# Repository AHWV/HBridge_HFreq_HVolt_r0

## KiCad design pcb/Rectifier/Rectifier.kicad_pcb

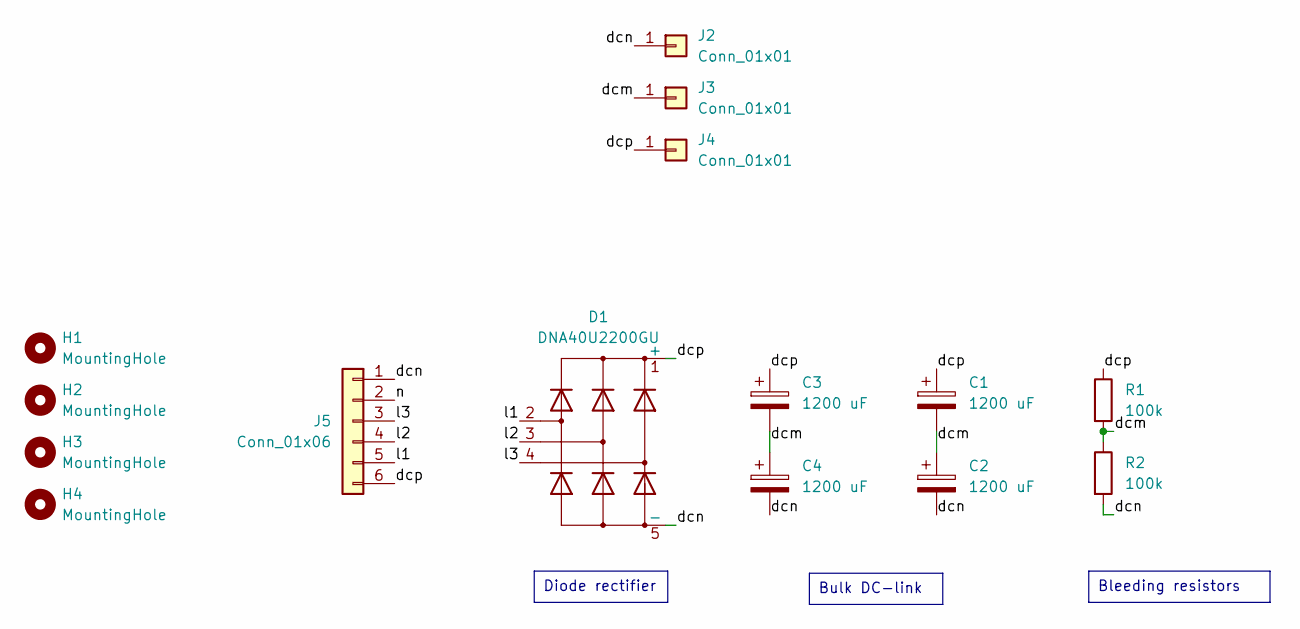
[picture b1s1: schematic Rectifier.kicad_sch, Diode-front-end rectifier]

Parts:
C1, C2, C3, C4: 1200 uF; CP_Radial_D35.0mm_P22.50mm_SnapIn_4Pin_TDK_B43630; Part # MAL229956122E3
D1: DNA40U2200GU; Diode_Bridge_IXYS_GUFP
H1, H2, H3, H4: MountingHole; MountingHole_2.7mm_M2.5
J2, J3, J4: Conn_01x01; WP_SMRA_7466303; Part # 7466303
J5: Conn_01x06; PhoenixContact_SPT_5_6-H-7.5-ZB_1x06_P7.5mm_Horizontal
R1, R2: 100k; R_Axial_DIN0617_L17.0mm_D6.0mm_P30.48mm_Horizontal

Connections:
/dcm: C1.2, C2.1, C3.2, C4.1, J3.1, R1.2, R2.1
/dcn: C2.2, C4.2, D1.5 (-), J2.1, J5.1, R2.2
/dcp: C1.1, C3.1, D1.1 (+), J4.1, J5.6, R1.1
/l1: D1.2, J5.5
/l2: D1.3, J5.4
/l3: D1.4, J5.3
/n: J5.2

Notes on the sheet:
Diode rectifier
Bulk DC-link
Bleeding resistors

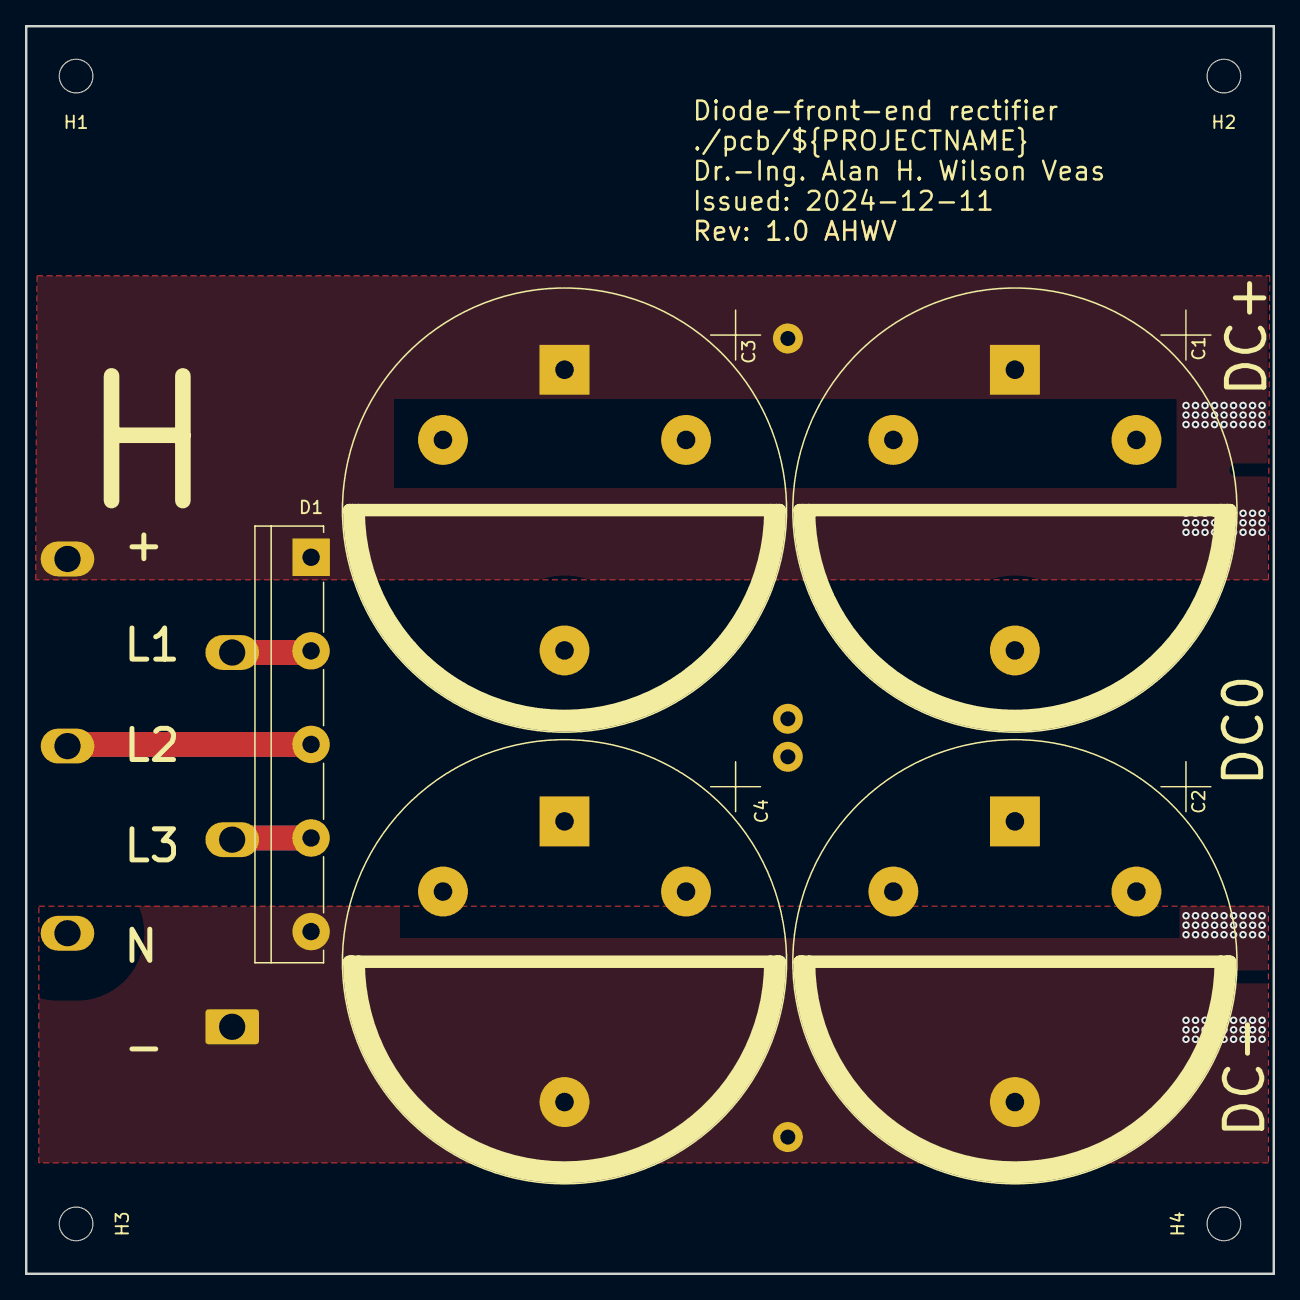
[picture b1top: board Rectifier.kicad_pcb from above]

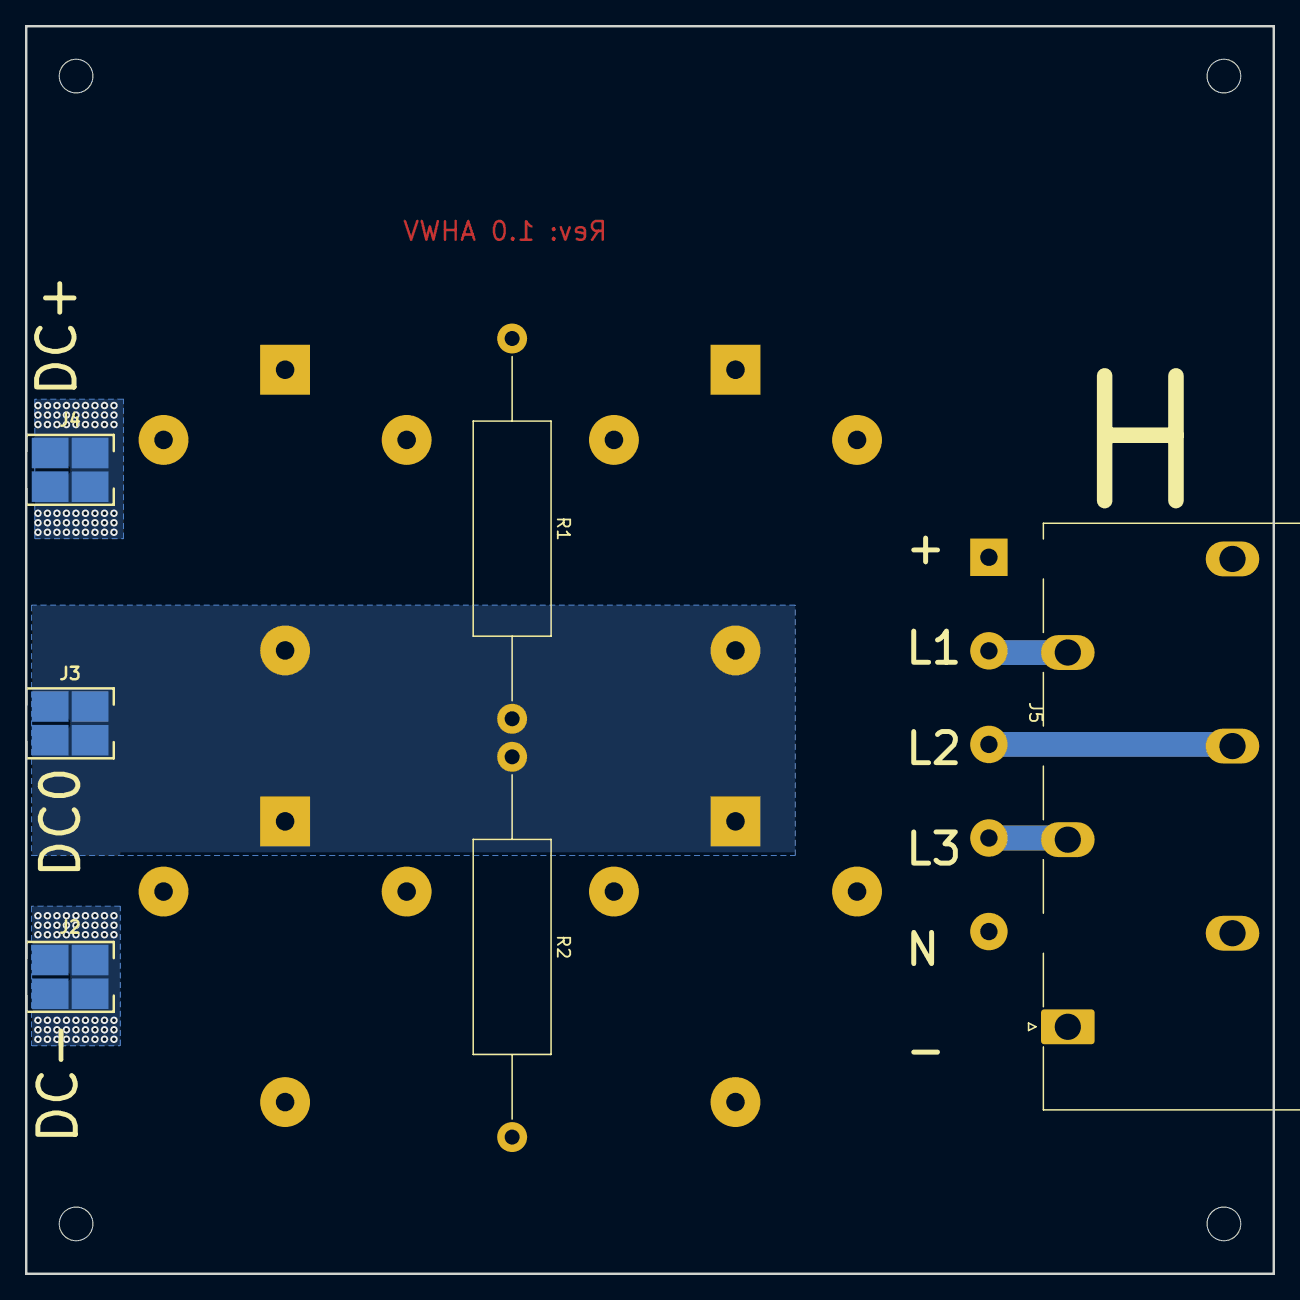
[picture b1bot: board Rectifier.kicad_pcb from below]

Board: 2 copper layers, 100.0 x 100.0 mm, 15 parts (6 on the bottom side), 6 nets.

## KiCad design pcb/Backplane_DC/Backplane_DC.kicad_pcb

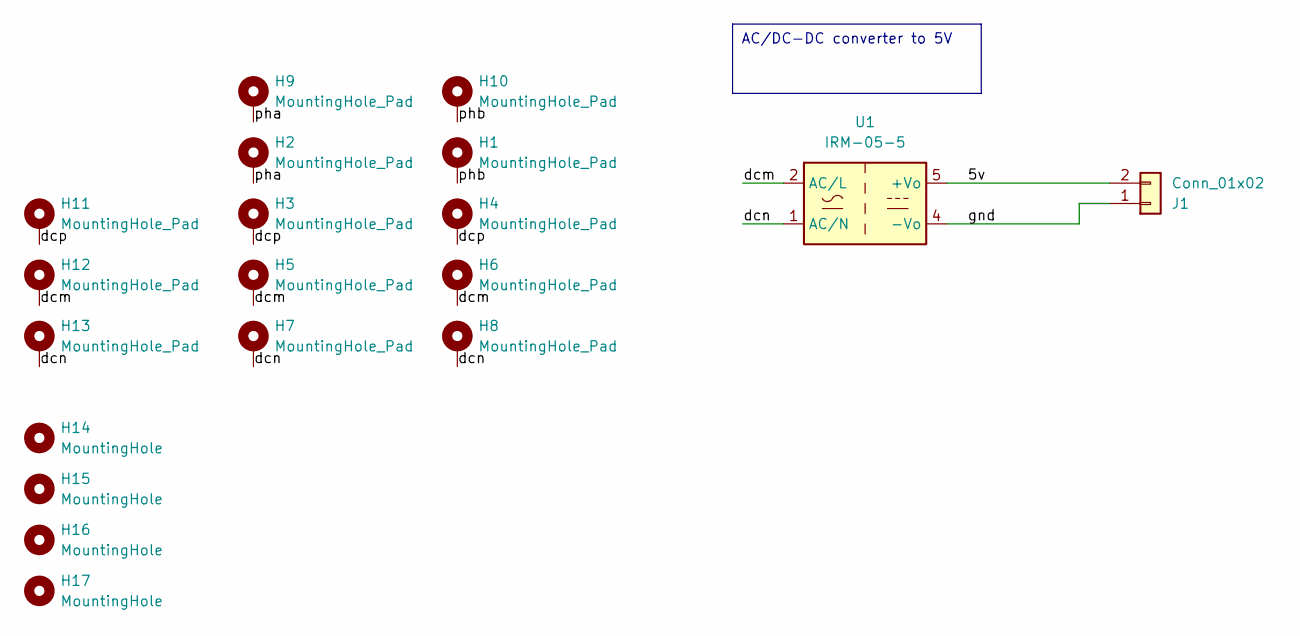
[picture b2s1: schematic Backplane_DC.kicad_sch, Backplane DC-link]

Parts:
H1, H2, H3, H4, H5, H6, H7, H8, H9, H10, H11, H12, H13: MountingHole_Pad; MountingHole_4.3mm_M4_DIN965_Pad
H14, H15, H16, H17: MountingHole; MountingHole_2.7mm_M2.5
J1: Conn_01x02; PhoenixContact_SPT_1.5_2-H-3.5_1x02_P3.5mm_Horizontal
U1: IRM-05-5

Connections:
/5v: J1.2, U1.5 (+Vo)
/dcm: H5.1, H6.1, H12.1, U1.2 (AC/L)
/dcn: H7.1, H8.1, H13.1, U1.1 (AC/N)
/dcp: H3.1, H4.1, H11.1
/gnd: J1.1, U1.4 (-Vo)
/pha: H2.1, H9.1
/phb: H1.1, H10.1

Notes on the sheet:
AC/DC-DC converter to 5V

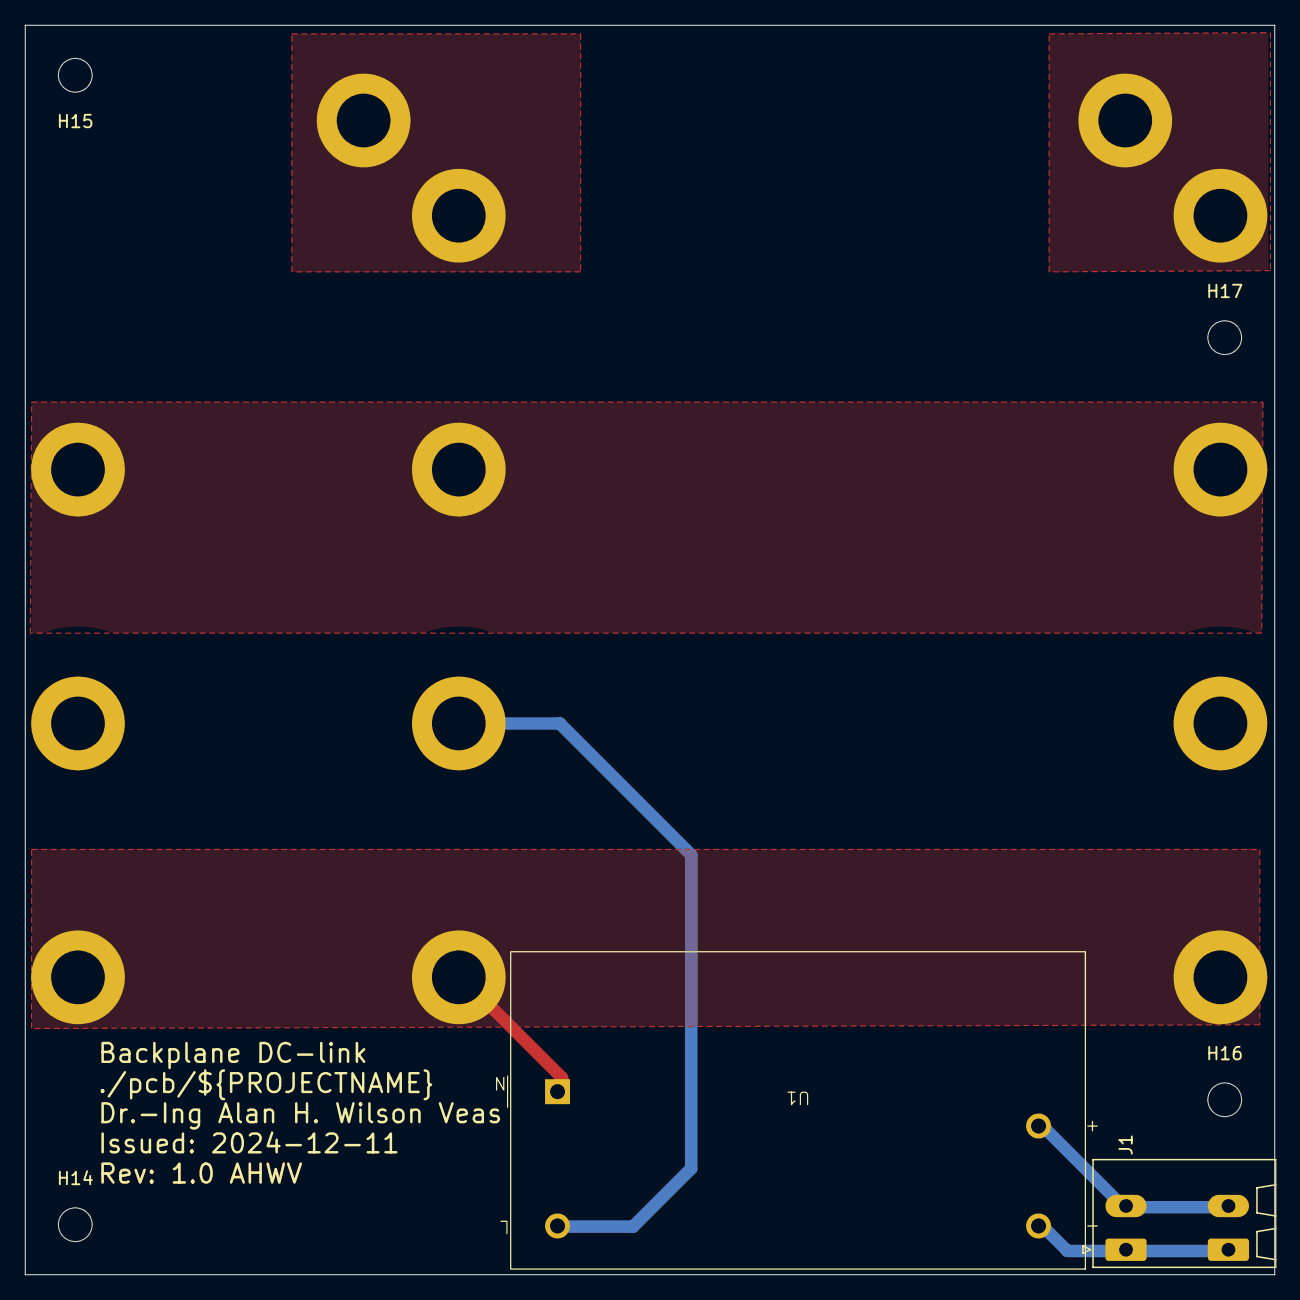
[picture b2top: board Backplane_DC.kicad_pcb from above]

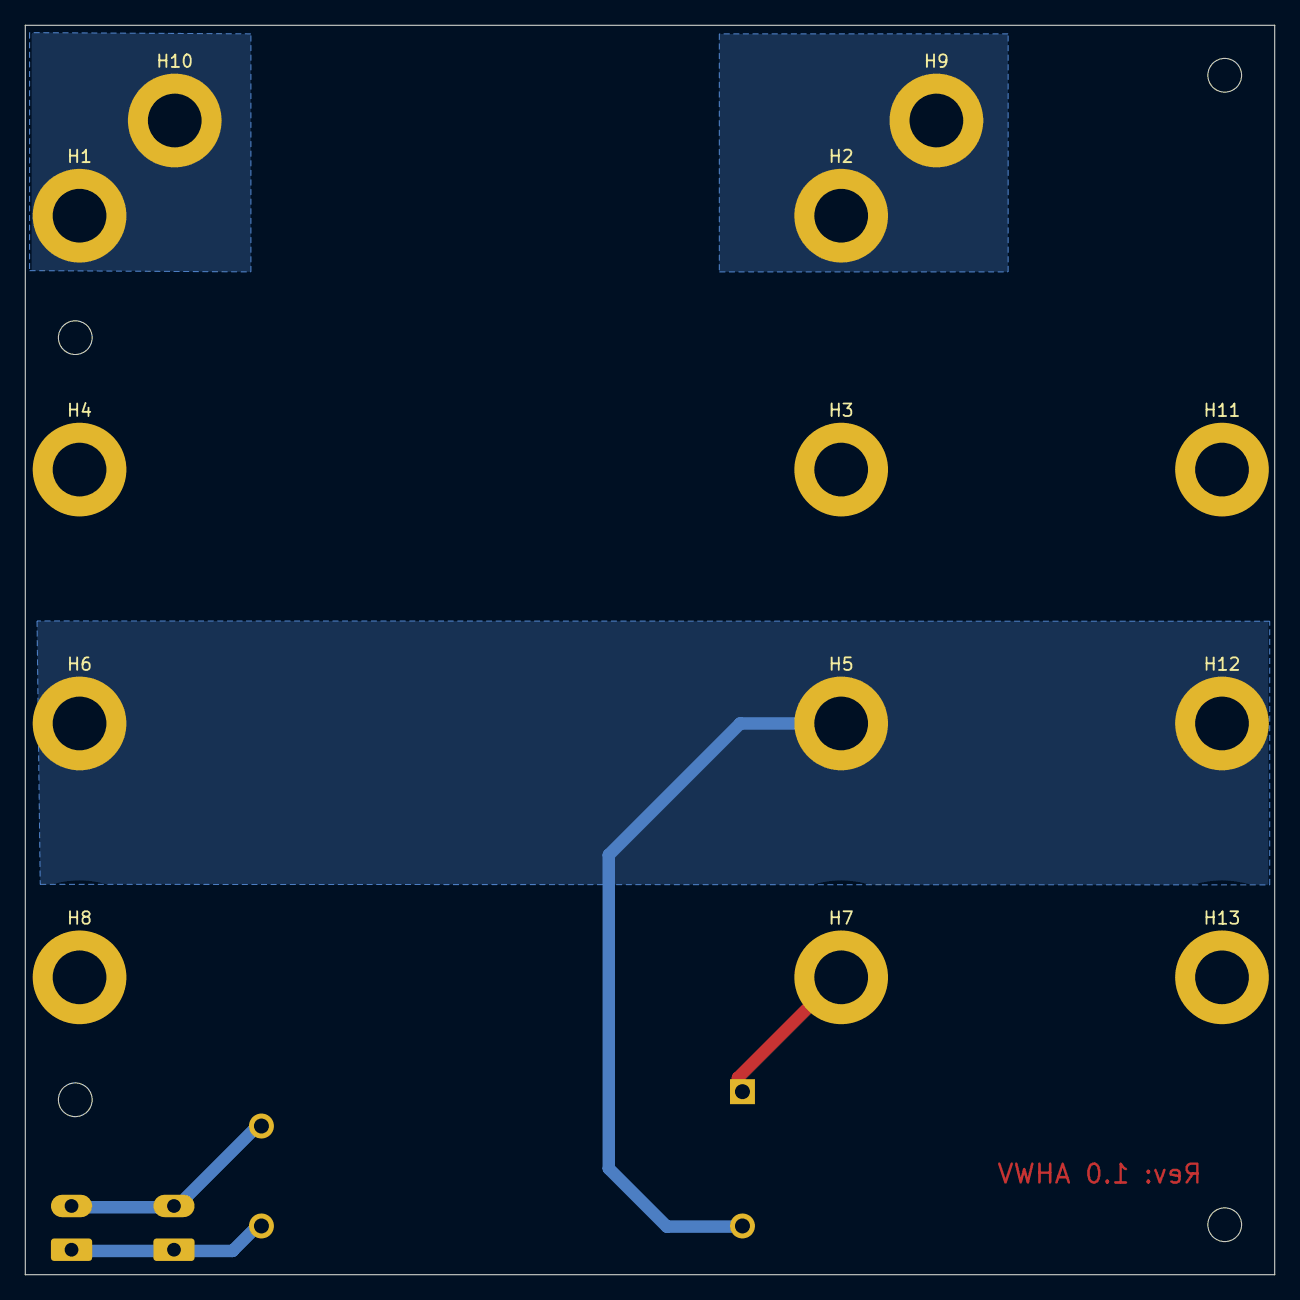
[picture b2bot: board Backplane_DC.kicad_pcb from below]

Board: 2 copper layers, 100.0 x 100.0 mm, 19 parts (13 on the bottom side), 7 nets.

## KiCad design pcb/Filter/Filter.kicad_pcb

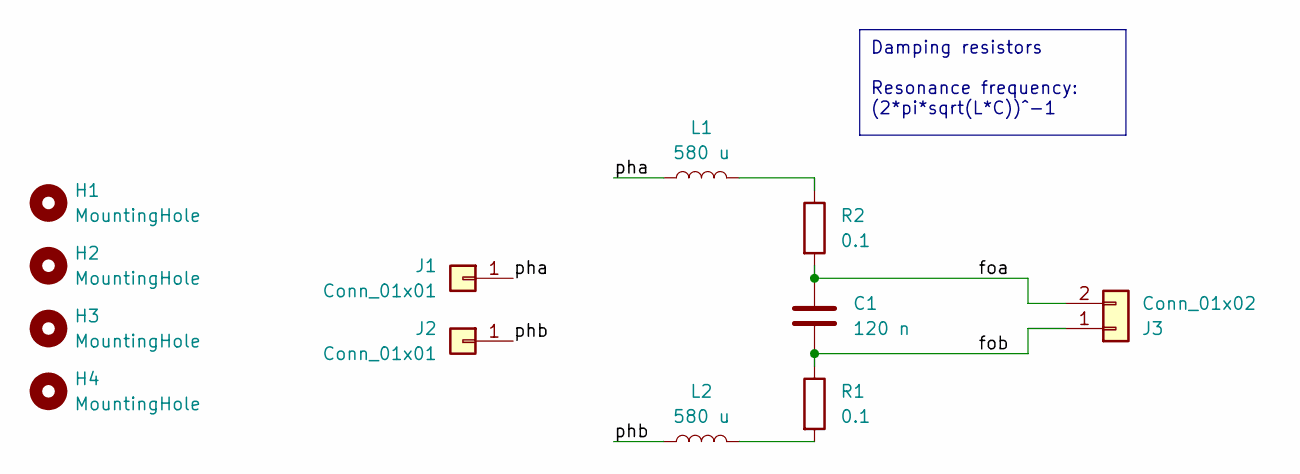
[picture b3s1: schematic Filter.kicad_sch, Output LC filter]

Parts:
C1: 120 n; C_Rect_L26.5mm_W11.5mm_P22.50mm_MKS4
H1, H2, H3, H4: MountingHole; MountingHole_2.7mm_M2.5
J1, J2: Conn_01x01; WP_SMRA_7466303; Part # 7466303
J3: Conn_01x02; PhoenixContact_SPT_5_2-H-7.5-ZB_1x02_P7.5mm_Horizontal
L1, L2: 580 u; L_Wuerth_WE-TORPFC_Diameter72.0mm_760801203
R1, R2: 0.1; R_Axial_DIN0617_L17.0mm_D6.0mm_P25.40mm_Horizontal

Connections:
/foa: C1.1, J3.2, R2.2
/fob: C1.2, J3.1, R1.1
/pha: J1.1, L1.1
/phb: J2.1, L2.1
unnamed: L1.2, R2.1
unnamed: L2.2, R1.2

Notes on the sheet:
Damping resistors Resonance frequency: (2*pi*sqrt(L*C))^-1

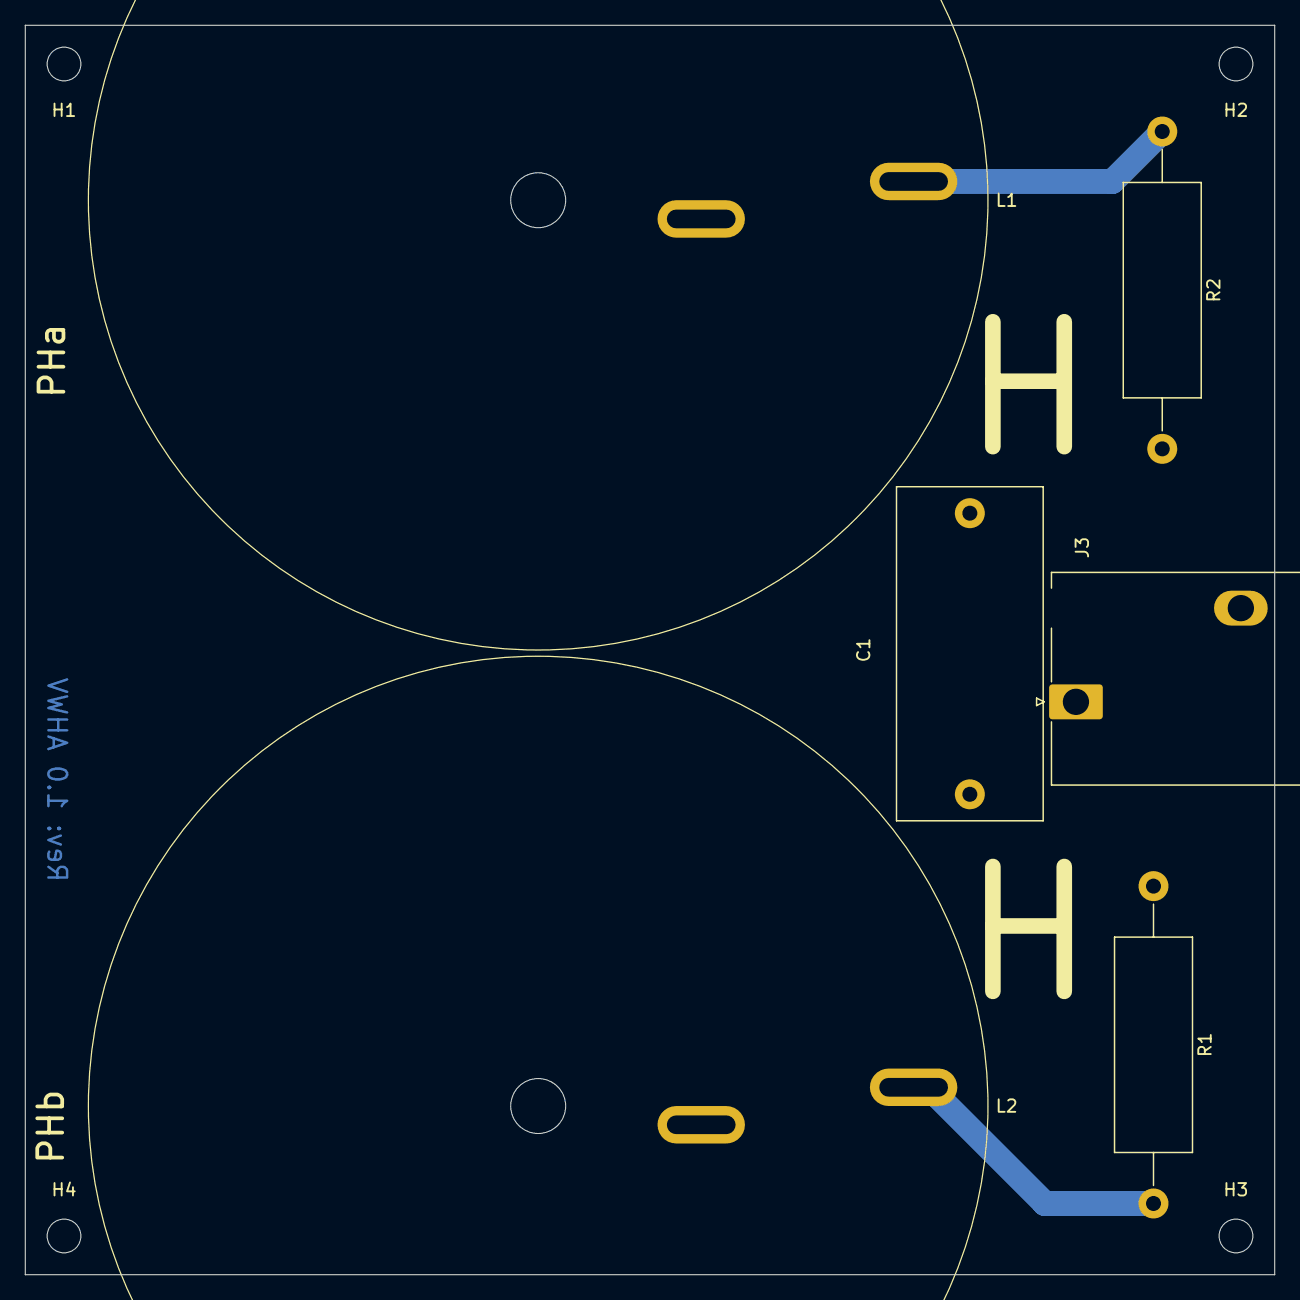
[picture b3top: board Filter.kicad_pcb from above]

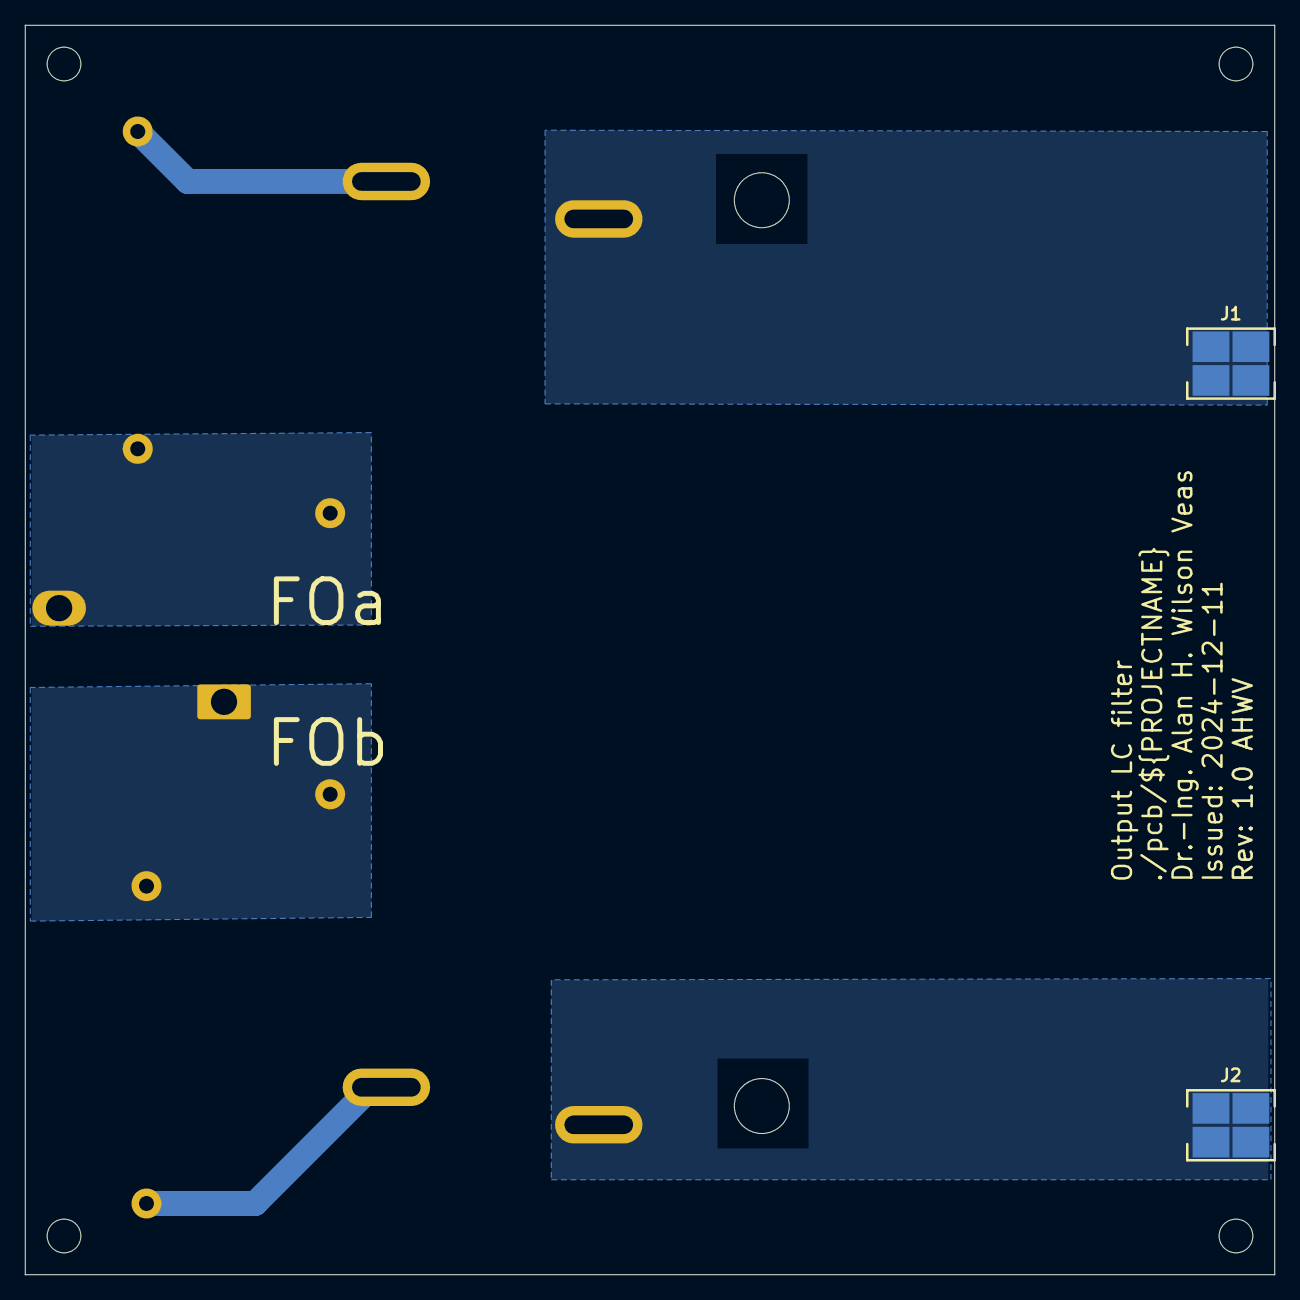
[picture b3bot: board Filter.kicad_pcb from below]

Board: 2 copper layers, 100.0 x 100.0 mm, 12 parts (2 on the bottom side), 6 nets.

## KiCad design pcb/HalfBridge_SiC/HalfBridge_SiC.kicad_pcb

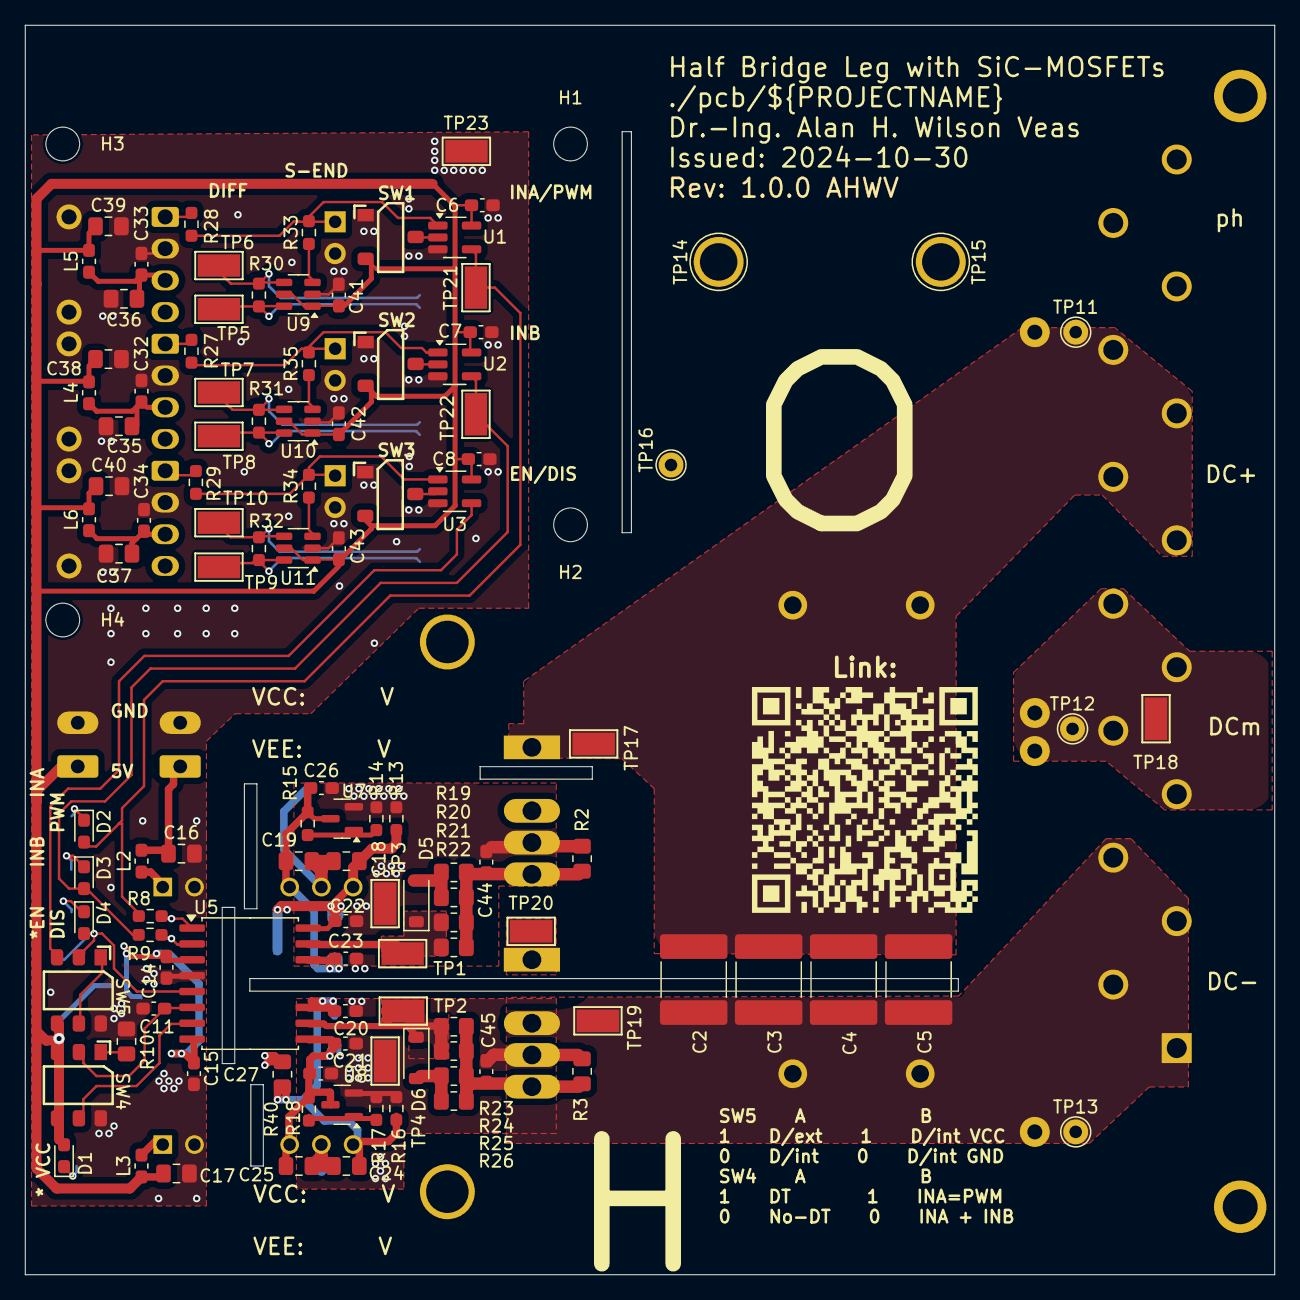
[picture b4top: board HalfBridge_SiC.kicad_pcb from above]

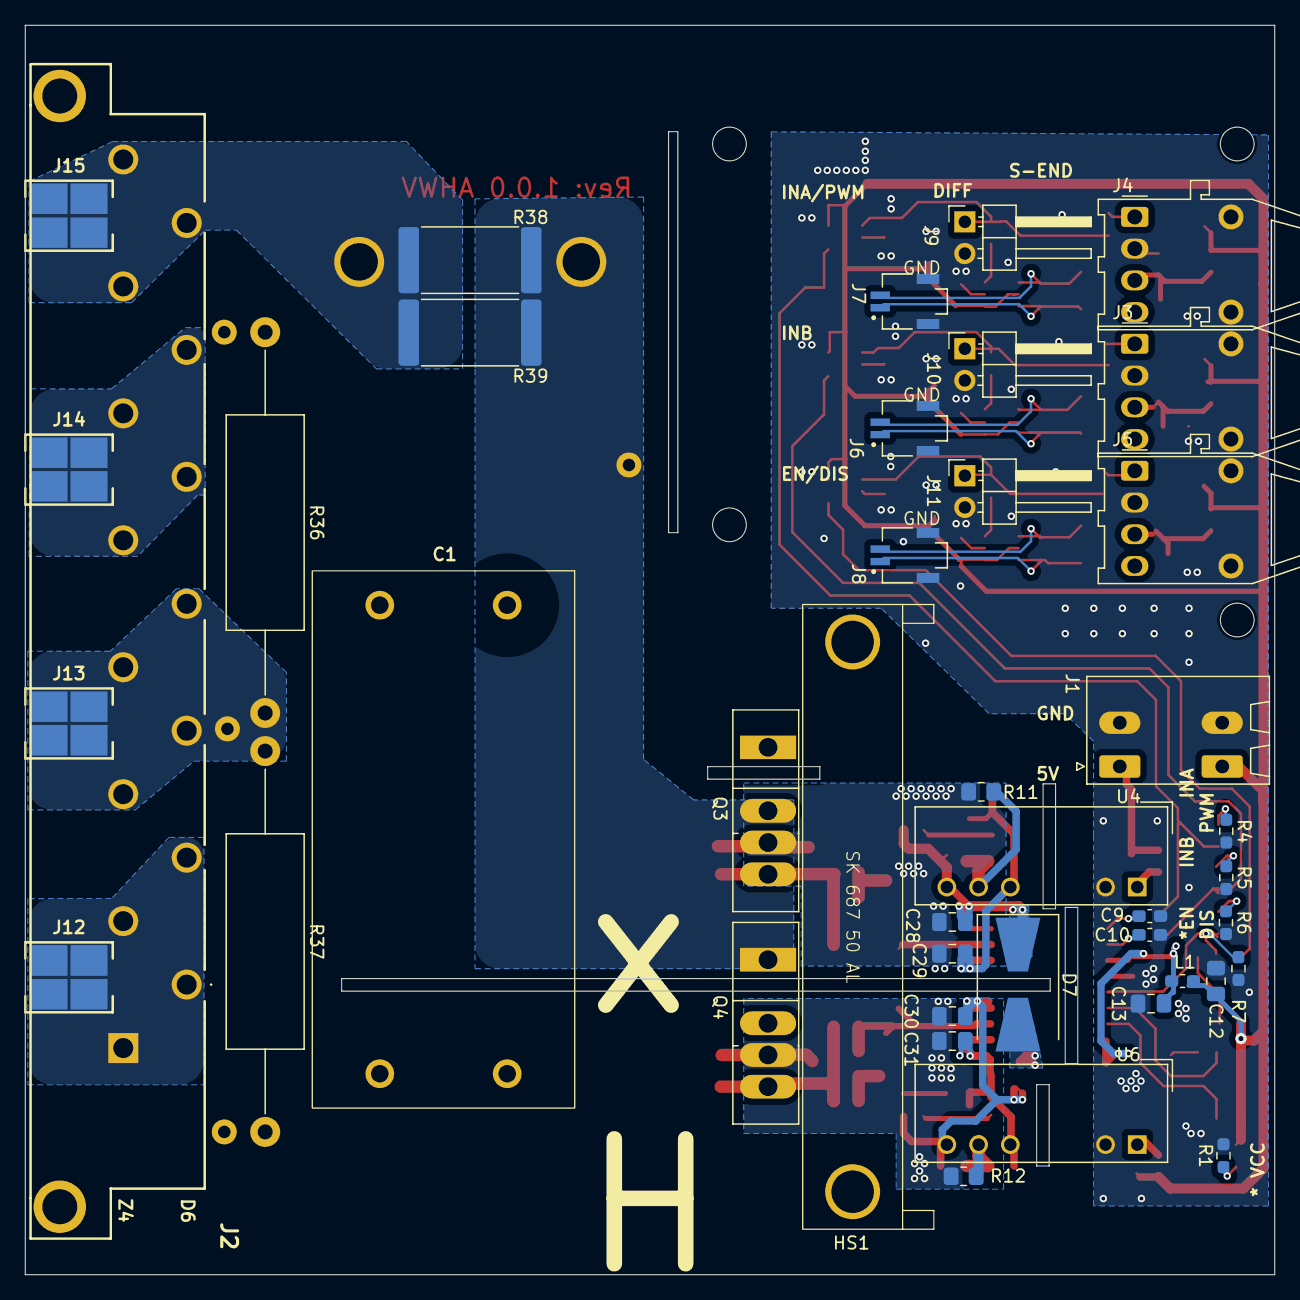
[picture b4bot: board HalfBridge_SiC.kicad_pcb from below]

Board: 2 copper layers, 100.0 x 100.0 mm, 160 parts (42 on the bottom side), 62 nets.

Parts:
C1: 10 u; C_Rect_L42.0mm_W20.0mm_PW37.50mm_PL10.2mm_C4AU
C2, C3, C4, C5: 100 n; C_2220_5750Metric_Pad1.97x5.40mm_HandSolder
C6, C7, C8, C11, C14, C15, C20, C21, C22, C23, C26, C27, C32, C33, C34, C41, C42, C43: 100n; C_0603_1608Metric_Pad1.08x0.95mm_HandSolder
C9, C10: 33p; C_0603_1608Metric_Pad1.08x0.95mm_HandSolder
C12, C13, C16, C17, C18, C19, C24, C25, C28, C29, C30, C31, C35, C36, C37, C38, C39, C40: 10u; C_0805_2012Metric_Pad1.18x1.45mm_HandSolder
C44, C45: 1n; C_0603_1608Metric_Pad1.08x0.95mm_HandSolder
D1, D2, D3, D4: LED; LED_0603_1608Metric_Pad1.05x0.95mm_HandSolder
D5, D6: D_Schottky; D_SOD-123
D7: D; D_SMB-SMC_Universal_Handsoldering
H1, H2, H3, H4: MountingHole; MountingHole_2.7mm_M2.5
HS1: Heatsink_Pad_2Pin; Heatsink_Fischer_SK687_50
J1: Conn_01x02; PhoenixContact_SPT_1.5_2-H-3.5_1x02_P3.5mm_Horizontal
J2: 413638-E; TEConnectivity_413638E
J3, J4, J5: AFBR-2624Z; Broadcom_AFBR-16xxZ_Horizontal
J6, J7, J8: Conn_01x02_Shielded; SAMTEC_T1M-02-F-SH-L-K
J9, J10, J11: Conn_01x02; PinHeader_1x02_P2.54mm_Horizontal
J12, J13, J14, J15: Conn_01x01; WP_SMRA_7466303
L1, L2, L3: 4.7u; L_0603_1608Metric_Pad1.05x0.95mm_HandSolder
L4, L5, L6: 1u; L_0603_1608Metric_Pad1.05x0.95mm_HandSolder
Link:: LOGO
Q3, Q4: C3M0040120K; TO-247-4_Vertical
R1, R4, R5, R6: 330; R_0603_1608Metric_Pad0.98x0.95mm_HandSolder
R2, R3: 10k; R_0805_2012Metric_Pad1.20x1.40mm_HandSolder
R7, R13, R14, R15, R16, R17, R18: R; R_0603_1608Metric_Pad0.98x0.95mm_HandSolder
R8, R9: 51; R_0603_1608Metric_Pad0.98x0.95mm_HandSolder
R10, R19, R20, R21, R22, R23, R24, R25, R26, R40: R; R_0805_2012Metric_Pad1.20x1.40mm_HandSolder
R11, R12: 0; R_0805_2012Metric_Pad1.20x1.40mm_HandSolder
R27, R28, R29, R33, R34, R35: 0; R_0603_1608Metric_Pad0.98x0.95mm_HandSolder
R30, R31, R32: 120; R_0603_1608Metric_Pad0.98x0.95mm_HandSolder
R36, R37: 100k; R_Axial_DIN0617_L17.0mm_D6.0mm_P30.48mm_Horizontal
R38, R39: 0; R_4020_10251Metric_Pad1.65x5.30mm_HandSolder
SW1, SW2, SW3: CAS-120X1; Nidec_Copal_CAS-120B1
SW4, SW5: CAS-D20X1; SW_SPDTx02_Slide_Copal_CAS-D20B1_W5.6mm_P1.7mm_GullW
TP1, TP2, TP3, TP4, TP5, TP6, TP7, TP8, TP9, TP10, TP21, TP22, TP23: TestPoint; TestPoint_Keystone_5015_Micro-Minature
TP11, TP12, TP13, TP16: TestPoint; TestPoint_THTPad_D2.0mm_Drill1.0mm
TP14, TP15: TestPoint; TestPoint_Plated_Hole_D3.0mm
TP17, TP18, TP19, TP20: TestPoint_Small; TestPoint_Keystone_5015_Micro-Minature
U1, U2, U3: 74AHC1G86; SOT-23-5_HandSoldering
U4, U6: RKD-052005D; Converter_DCDC_RECOM_RKZ-xx2005_Dual_THT_SIP7
U5: NCV51563; SOIC-16W_7.5x10.3mm_P1.27mm_NoPin_12_13
U7, U8: TL432DBZ; SOT-23
U9, U10, U11: MAX3284E; SOT-23-6

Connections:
/HalfBridge_Diff/gnd: C6.2, C7.2, C8.2, C9.2, C10.2, C11.2, C12.2, C13.2, C14.2, C15.2, C16.2, C17.2, C32.2, C33.2, C34.2, C35.2, C36.2, C37.2, C38.2, C39.2, C40.2, C41.2, C42.2, C43.2, J1.2, J3.2 (VEER), J3.5 (HP), J3.8 (HP), J4.2 (VEER), J4.5 (HP), J4.8 (HP), J5.2 (VEER), J5.5 (HP), J5.8 (HP), J6.SH (Shield), J7.SH (Shield), J8.SH (Shield), J9.2, J10.2, J11.2, R1.2, R4.2, R5.2, R6.2, R7.2, R10.1, SW1.1 (A), SW2.1 (A), SW3.1 (A), SW4.4 (A), SW5.4 (A), TP23.1, U1.3 (GND), U2.3 (GND), U3.3 (GND), U4.2 (VIN-), U5.4 (GND), U6.2 (VIN-), U9.2 (GND), U10.2 (GND), U11.2 (GND)
/HalfBridge_Diff/ina_d: J9.1, R28.1, R33.2, U1.1
/HalfBridge_Diff/ina_da: J7.1, R30.1, TP5.1, U9.6 (A)
/HalfBridge_Diff/ina_db: J7.2, R30.2, TP6.1, U9.4 (B)
/HalfBridge_Diff/ina_nd: R33.1, U9.3 (RO)
/HalfBridge_Diff/inb_d: J10.1, R27.1, R35.2, U2.1
/HalfBridge_Diff/inb_da: J6.1, R31.1, TP7.1, U10.6 (A)
/HalfBridge_Diff/inb_db: J6.2, R31.2, TP8.1, U10.4 (B)
/HalfBridge_Diff/inb_nd: R35.1, U10.3 (RO)
/HalfBridge_Diff/inen_d: J11.1, R29.1, R34.2, U3.1
/HalfBridge_Diff/inen_da: J8.1, R32.1, TP9.1, U11.6 (A)
/HalfBridge_Diff/inen_db: J8.2, R32.2, TP10.1, U11.4 (B)
/HalfBridge_Diff/inen_nd: R34.1, U11.3 (RO)
/HalfBridge_Diff/vcc: C6.1, C7.1, C8.1, C12.1, C16.1, C17.1, C38.1, C39.1, C40.1, C41.1, C42.1, C43.1, D1.2 (A), J1.1, L1.1, L2.1, L3.1, L4.2, L5.2, L6.2, SW1.3 (C), SW2.3 (C), SW3.3 (C), SW4.3 (C), SW4.6 (C), SW5.6 (C), U1.5 (VCC), U2.5 (VCC), U3.5 (VCC), U9.1 (VCC), U9.5 (VL), U10.1 (VCC), U10.5 (VL), U11.1 (VCC), U11.5 (VL)
/HalfBridge_GateDriver/adjh: R14.1, R15.2, U7.1 (REF)
/HalfBridge_GateDriver/adjl: R17.1, R18.2, U8.1 (REF)
/HalfBridge_GateDriver/anb: SW4.5 (B), U5.7 (ANB)
/HalfBridge_GateDriver/asgh: D5.2 (A), R19.1, R20.1
/HalfBridge_GateDriver/asgl: D6.2 (A), R25.1, R26.1
/HalfBridge_GateDriver/bootR: D7.2 (A), R40.1
/HalfBridge_GateDriver/comh: C18.2, C19.1, R11.1, U4.6 (COM)
/HalfBridge_GateDriver/coml: C24.2, C25.1, R12.1, U6.6 (COM)
/HalfBridge_GateDriver/dis: D4.2 (A), R7.1, SW5.2 (B), U5.5 (DIS)
/HalfBridge_GateDriver/dis_i: SW5.1 (A), SW5.5 (B)
/HalfBridge_GateDriver/dis_x: SW5.3 (C), U3.4
/HalfBridge_GateDriver/dt: C11.1, SW4.2 (B), U5.6 (DT)
/HalfBridge_GateDriver/gonh: D5.1 (K), R21.1, R22.1, TP1.1, U5.15 (OUTA)
/HalfBridge_GateDriver/gonl: D6.1 (K), R23.1, R24.1, TP2.1, U5.10 (OUTB)
/HalfBridge_GateDriver/inaf: C9.1, R8.2, U5.1 (INA)
/HalfBridge_GateDriver/inbf: C10.1, R9.2, U5.2 (INB)
/HalfBridge_GateDriver/inga: D2.2 (A), R8.1, TP21.1, U1.4
/HalfBridge_GateDriver/ingb: D3.2 (A), R9.1, TP22.1, U2.4
/HalfBridge_GateDriver/kh: C22.2, C23.1, C26.1, C28.2, C29.1, C44.2, Q3.3 (DS), R2.2, R11.2, R13.1, R14.2, TP3.1, U7.2 (K)
/HalfBridge_GateDriver/kl: C20.2, C21.1, C27.1, C30.2, C31.1, C45.2, Q4.3 (DS), R3.2, R12.2, R16.1, R17.2, TP4.1, U8.2 (K)
/HalfBridge_GateDriver/lrdis: D4.1 (K), R6.1
/HalfBridge_GateDriver/lringa: D2.1 (K), R4.1
/HalfBridge_GateDriver/lringb: D3.1 (K), R5.1
/HalfBridge_GateDriver/rdt: R10.2, SW4.1 (A)
/HalfBridge_GateDriver/vcci: C13.1, C14.1, C15.1, L1.2, U5.3 (VCCI), U5.8 (VCCI)
/HalfBridge_GateDriver/vddh: C18.1, C22.1, C28.1, D7.1 (K), R13.2, U4.7 (+VDC), U5.16 (VDDA)
/HalfBridge_GateDriver/vddl: C20.1, C24.1, C30.1, R16.2, R40.2, U5.11 (VDDB), U6.7 (+VDC)
/HalfBridge_GateDriver/vindc+h: L2.2, U4.1 (VIN+)
/HalfBridge_GateDriver/vindc+l: L3.2, U6.1 (VIN+)
/HalfBridge_GateDriver/vssh: C19.2, C23.2, C26.2, C29.2, R15.1, U4.5 (-VDC), U5.14 (VSSA), U7.3 (A)
/HalfBridge_GateDriver/vssl: C21.2, C25.2, C27.2, C31.2, R18.1, U5.9 (VSSB), U6.5 (-VDC), U8.3 (A)
/HalfBridge_GateDriver/xorina: SW1.2 (B), U1.2
/HalfBridge_GateDriver/xorinb: SW2.2 (B), U2.2
/HalfBridge_GateDriver/xorinen: SW3.2 (B), U3.2
/HalfBridge_Optical/oina: J4.1 (Data_Out), R28.2
/HalfBridge_Optical/oinb: J3.1 (Data_Out), R27.2
/HalfBridge_Optical/oinen: J5.1 (Data_Out), R29.2
/HalfBridge_Optical/vcca: C33.1, C36.1, J4.3 (VCCR), L5.1
/HalfBridge_Optical/vccb: C32.1, C35.1, J3.3 (VCCR), L4.1
/HalfBridge_Optical/vccen: C34.1, C37.1, J5.3 (VCCR), L6.1
/HalfBridge_Power/gh: C44.1, Q3.4 (G), R2.1, R19.2, R20.2, R21.2, R22.2
/HalfBridge_Power/gl: C45.1, Q4.4 (G), R3.1, R23.2, R24.2, R25.2, R26.2
/dcm: J2.D14, J2.D18, J2.Z12, J2.Z16, J13.1, R36.2, R37.1, TP12.1, TP18.1
/dcn: C1.2, C2.2, C3.2, C4.2, C5.2, J2.D6, J2.D10, J2.Z4, J2.Z8, J12.1, Q4.2 (S), R37.2, TP13.1, TP19.1
/dcp: C1.1, C2.1, C3.1, C4.1, C5.1, J2.D22, J2.D26, J2.Z20, J2.Z24, J14.1, Q3.1 (D), R36.1, TP11.1, TP17.1
/lvcc: D1.1 (K), R1.1
/ph: Q3.2 (S), Q4.1 (D), R38.1, R39.1, TP14.1, TP16.1, TP20.1
/pho: J2.D30, J2.Z28, J2.Z32, J15.1, R38.2, R39.2, TP15.1

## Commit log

2024-10-21 first
2024-10-28 pcb + horizontal of
2024-10-30 vgatereg + route + hsink
2024-10-30 comment + gdriver + logo
2024-10-30 2DPDT switch footprint
2024-11-04 vcc label
2024-11-05 part number
2024-11-10 backplane
2024-11-12 local lib
2024-11-13 pcb + newlib
2024-11-13 no step file
2024-11-19 backplane + external lib
2024-12-03 update lib
2024-12-10 filter + sim + assembly3d
2024-12-10 filter + backplane
2024-12-11 designator + part n°
2024-12-11 new 3d filter
2024-12-12 titles
